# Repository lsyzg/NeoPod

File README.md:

# NeoPod
<hl></hl>
### A modern, bluetooth compatible handheld music player

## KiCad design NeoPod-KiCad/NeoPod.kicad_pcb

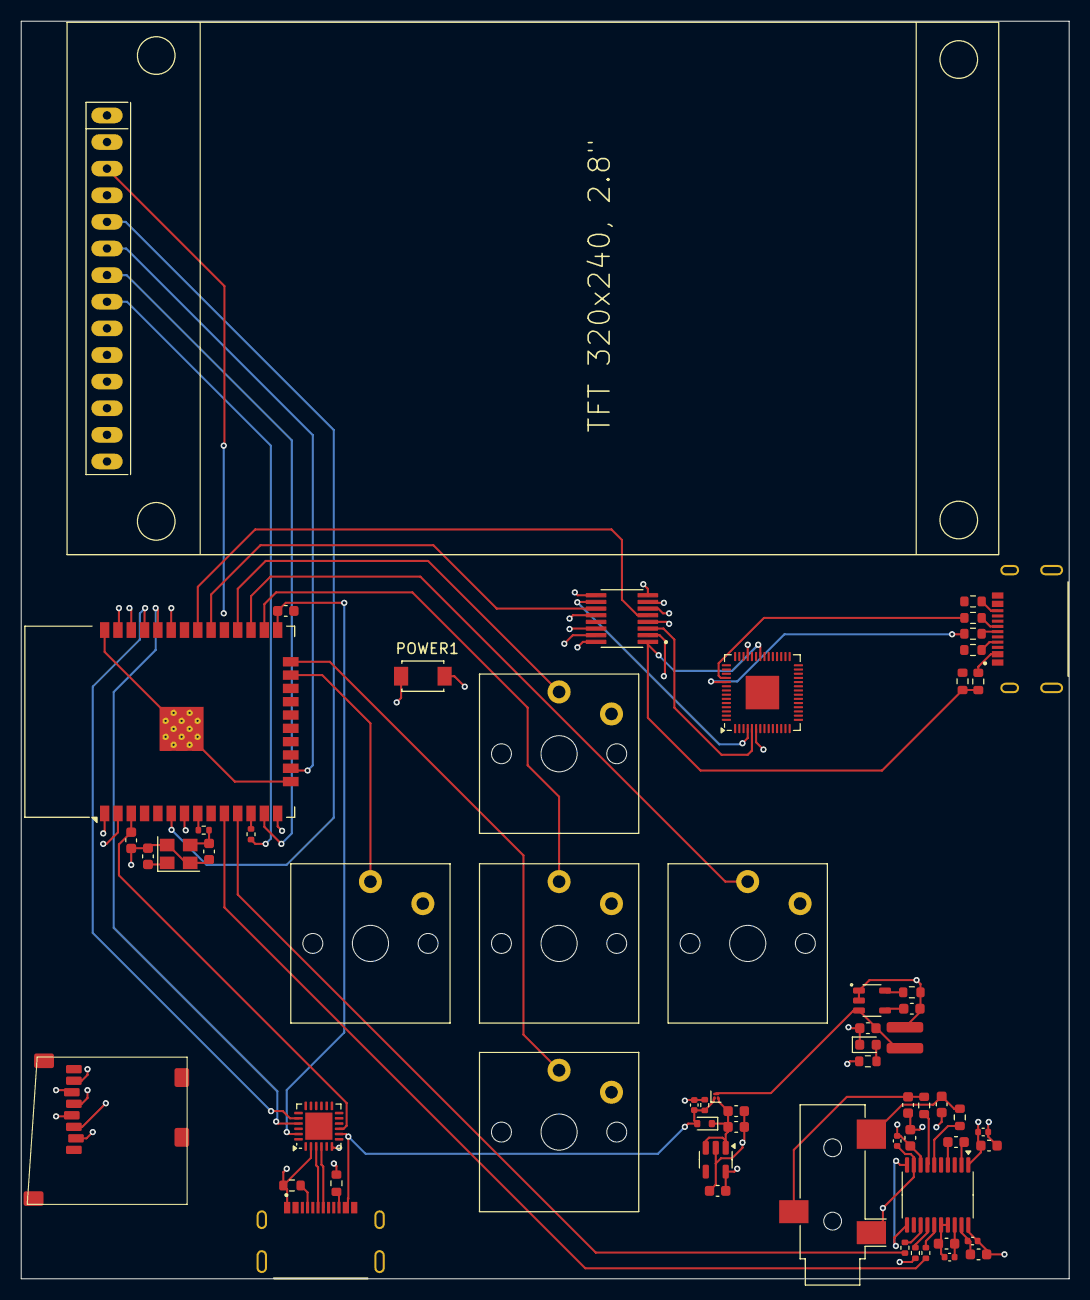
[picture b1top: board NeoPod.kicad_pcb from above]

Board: 4 copper layers, 100.0 x 120.0 mm, 62 parts (0 on the bottom side), 66 nets.

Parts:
BT1: Battery_Cell; JST_PH_S2B-PH-SM4-TB_1x02-1MP_P2.00mm_Horizontal
C1, C7, C9, C10, C14, C15: 0.1uF; C_0603_1608Metric
C2, C6, C8, C11: 10uF; C_0402_1005Metric
C3, C4: 2.2nF; C_0603_1608Metric
C5, C24, C27, C28, C29, C30: 2.2uF; C_0603_1608Metric
C12, C13: 18pF; C_0603_1608Metric
C26: 100nF; C_0402_1005Metric
D1: MSK4005; D_SOD-523
D2: LED; LED_0603_1608Metric
J1: SJ-3523-SMT-TR; Jack_3.5mm_CUI_SJ-3523-SMT_Horizontal
J2, J4: USB4500-03-0-A_REVA1; GCT_USB4500-03-0-A_REVA1
POWER1: SW6; SW_TS-1088-AR02016
Q1: CSD25480F3; Texas_PicoStar_DFN-3_0.69x0.60mm
R1, R2: 470; R_0603_1608Metric
R3, R4, R5: 22; R_0402_1005Metric
R6: 0k; R_0402_1005Metric
R7, R8: 22k; R_0603_1608Metric
R9, R10, R13, R14: 5.1k; R_0603_1608Metric
R11: 10k; R_0603_1608Metric
R12: 20k; R_0603_1608Metric
R15: 100k; R_0402_1005Metric
R16: 2.7k; R_0603_1608Metric
R17: 2.2k; R_0603_1608Metric
R18: 100; R_0402_1005Metric
SW1, SW2, SW3, SW4, SW5: SW_SPST; Choc_V1
U1: ESP32-WROOM-32
U2: PCM5102A; TSSOP-20_4.4x6.5mm_P0.65mm
U3: RP2040; QFN-56-1EP_7x7mm_P0.4mm_EP3.2x3.2mm
U4: CP2102N-Axx-xQFN24; QFN-24-1EP_4x4mm_P0.5mm_EP2.6x2.6mm
U5: XC6210B332MR; SOT-23-5
U6: STC4054GR; SOT95P280X110-5N
U7: TFT_320x240; TFT-320x240
U10: SN74CB3Q3257DBQR
X1: MicroSD_Socket
Y2: 40MHz-Xtal; Crystal_SMD_3225-4Pin_3.2x2.5mm

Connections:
BCK: R5.1, U1.11 (IO26)
CS-ESP32: U1.33 (IO21), U10.14 (4B1)
CS-SD: U10.12 (4A), X1.2 (CD/DAT3)
CS-TFT: U1.29 (IO5), U7.3 (CS)
D+: J2.A6 (DP1), J2.B6 (DP2), U4.3 (D+)
D-: J2.A7 (DN1), J2.B7 (DN2), U4.4 (D-)
DC-TFT: U1.6 (IO34), U7.5 (DC)
DIN: R4.1, U1.36 (IO22)
DM: J4.A7 (DN1), J4.B7 (DN2), R8.1
DP: J4.A6 (DP1), J4.B6 (DP2), R7.1
DTR: C14.2, U1.25 (IO0), U4.23 (~DTR)
EN - ESP32: C15.2, U1.3 (EN), U4.9 (~RST)
ESP_USB_DM: R8.2, U3.46 (USB_DM)
ESP_USB_DP: R7.2, U3.47 (USB_DP)
GND: BT1.2 (-), C6.1, C7.1, C8.2, C9.2, C12.1, C13.2, C14.1, C15.1, C24.1, C26.2, C27.2, C28.2, C29.2, C30.2, D2.1 (K), J2.A1_B12 (GND_A), J2.B1_A12 (GND_B), J2.SH1 (SHELL_GND), J2.SH2 (SHELL_GND), J2.SH3 (SHELL_GND), J2.SH4 (SHELL_GND), J4.A1_B12 (GND_A), J4.B1_A12 (GND_B), J4.SH1 (SHELL_GND), J4.SH2 (SHELL_GND), J4.SH3 (SHELL_GND), J4.SH4 (SHELL_GND), POWER1.2 (B), R9.1, R10.2, R12.2, R13.2, R14.2, R15.2, R16.1, SW1.2 (B), SW2.2 (B), SW3.2 (B), SW4.2 (B), SW5.2 (B), U1.1 (GND), U1.15 (GND), U1.38 (GND), U1.39 (GND), U2.10 (DEMP), U2.11 (FLT), U2.16 (FMT), U2.17 (XSMT), U2.19 (DGND), U3.57 (GND), U4.2 (GND), U4.25 (GND), U5.2 (GND), U6.1 (CHRG), U6.2 (GND), U7.2 (GND), U10.8 (GND), U10.15 (OE), X1.6 (VSS), Y2.2, Y2.4
GNDREF: C1.2, C2.2, C3.1, C4.2, C10.1, C11.1, J1.1, U2.9 (AGND)
LED-TFT: R18.1, U7.8 (LED)
LRCK: R3.1, U1.10 (IO25)
MISO-ESP32: U1.31 (IO19), U10.5 (2B1)
MISO-RP2040: U3.6 (GPIO4), U10.6 (2B2)
MISO-SD: U10.7 (2A), X1.7 (DAT0)
MISO-TFT: U1.14 (IO12), U7.9 (MISO)
MOSI-ESP32: U1.37 (IO23), U10.2 (1B1)
MOSI-RP2040: U3.5 (GPIO3), U10.3 (1B2)
MOSI-SD: U10.4 (1A), X1.3 (CMD)
MOSI-TFT: U1.16 (IO13), U7.6 (MOSI)
unnamed: C3.2, J1.2, R2.2
unnamed: C4.1, J1.3, R1.2
unnamed: C12.2, R6.1, Y2.3
unnamed: C27.1, C28.1, D1.1 (K), Q1.2 (S), U5.1 (VIN), U5.3 (CE)
unnamed: D2.2 (A), R17.1
unnamed: J2.A5 (CC1), R13.1
unnamed: J2.B5 (CC2), R14.1
unnamed: J4.A5 (CC1), R10.1
unnamed: J4.B5 (CC2), R9.2
unnamed: POWER1.1 (A), U1.7 (IO35)
unnamed: R18.2, U1.12 (IO27)
unnamed: R6.2, U1.8 (IO32)
unnamed: C13.1, U1.9 (IO33), Y2.1
unnamed: R5.2, U2.13 (BCK)
unnamed: C5.2, U2.4 (CAPM)
unnamed: C5.1, U2.2 (CAPP)
unnamed: R4.2, U2.14 (DIN)
unnamed: C6.2, C7.2, U2.18 (LDOO)
unnamed: R3.2, U2.15 (LRCK)
unnamed: R2.1, U2.6 (OUTL)
unnamed: R1.1, U2.7 (OUTR)
unnamed: R16.2, U6.5 (PROG)
unnamed: C30.1, U6.4 (VCC)
RXD-U0TXD: U1.35 (TXD0/IO1), U4.20 (RXD)
SCK-ESP32: U1.30 (IO18), U10.11 (3B1)
SCK-RP2040: U3.4 (GPIO2), U10.10 (3B2)
SCK-SD: U10.9 (3A), X1.5 (CLK)
SCK-TFT: U1.13 (IO14), U7.7 (SCK)
SEL: R11.2, R12.1, U3.36 (GPIO24), U10.1 (SEL)
SW1: SW1.1 (A), U1.24 (IO2)
SW2: SW2.1 (A), U1.26 (IO4)
SW3: SW3.1 (A), U1.23 (IO15)
SW4: SW4.1 (A), U1.27 (IO16)
SW5: SW5.1 (A), U1.28 (IO17)
TXD-U0RXD: U1.34 (RXD0/IO3), U4.21 (TXD)
VBAT: BT1.1 (+), C24.2, Q1.3 (D), U6.3 (BAT)
VBUS-ESP32: C26.1, D1.2 (A), J2.A4_B9 (VBUS_A), J2.B4_A9 (VBUS_B), Q1.1 (G), R15.1, U4.8 (VBUS)
VBUS-RP2040: J4.A4_B9 (VBUS_A), J4.B4_A9 (VBUS_B), R11.1
VCC3v3: C8.1, C9.1, C29.1, R17.2, U1.2 (VDD), U2.20 (DVDD), U3.39 (GPIO27_ADC1), U4.6 (VDD), U5.5 (VOUT), U7.1 (VCC), U7.4 (RST), U10.16 (VCC), X1.4 (VDD)
VCC3v3a: C1.1, C2.1, C10.2, C11.2, U2.1 (CPVDD), U2.8 (AVDD)

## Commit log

2025-05-25 5/24/25 - Update JOURNAL.md
2025-05-25 started schematic
2025-05-26 finished schematic and added picture of finished schematic
2025-05-26 pdf plotting
2025-05-27 Started pcb layout and added images
2025-06-01 finished pcb
2025-08-06 small change
